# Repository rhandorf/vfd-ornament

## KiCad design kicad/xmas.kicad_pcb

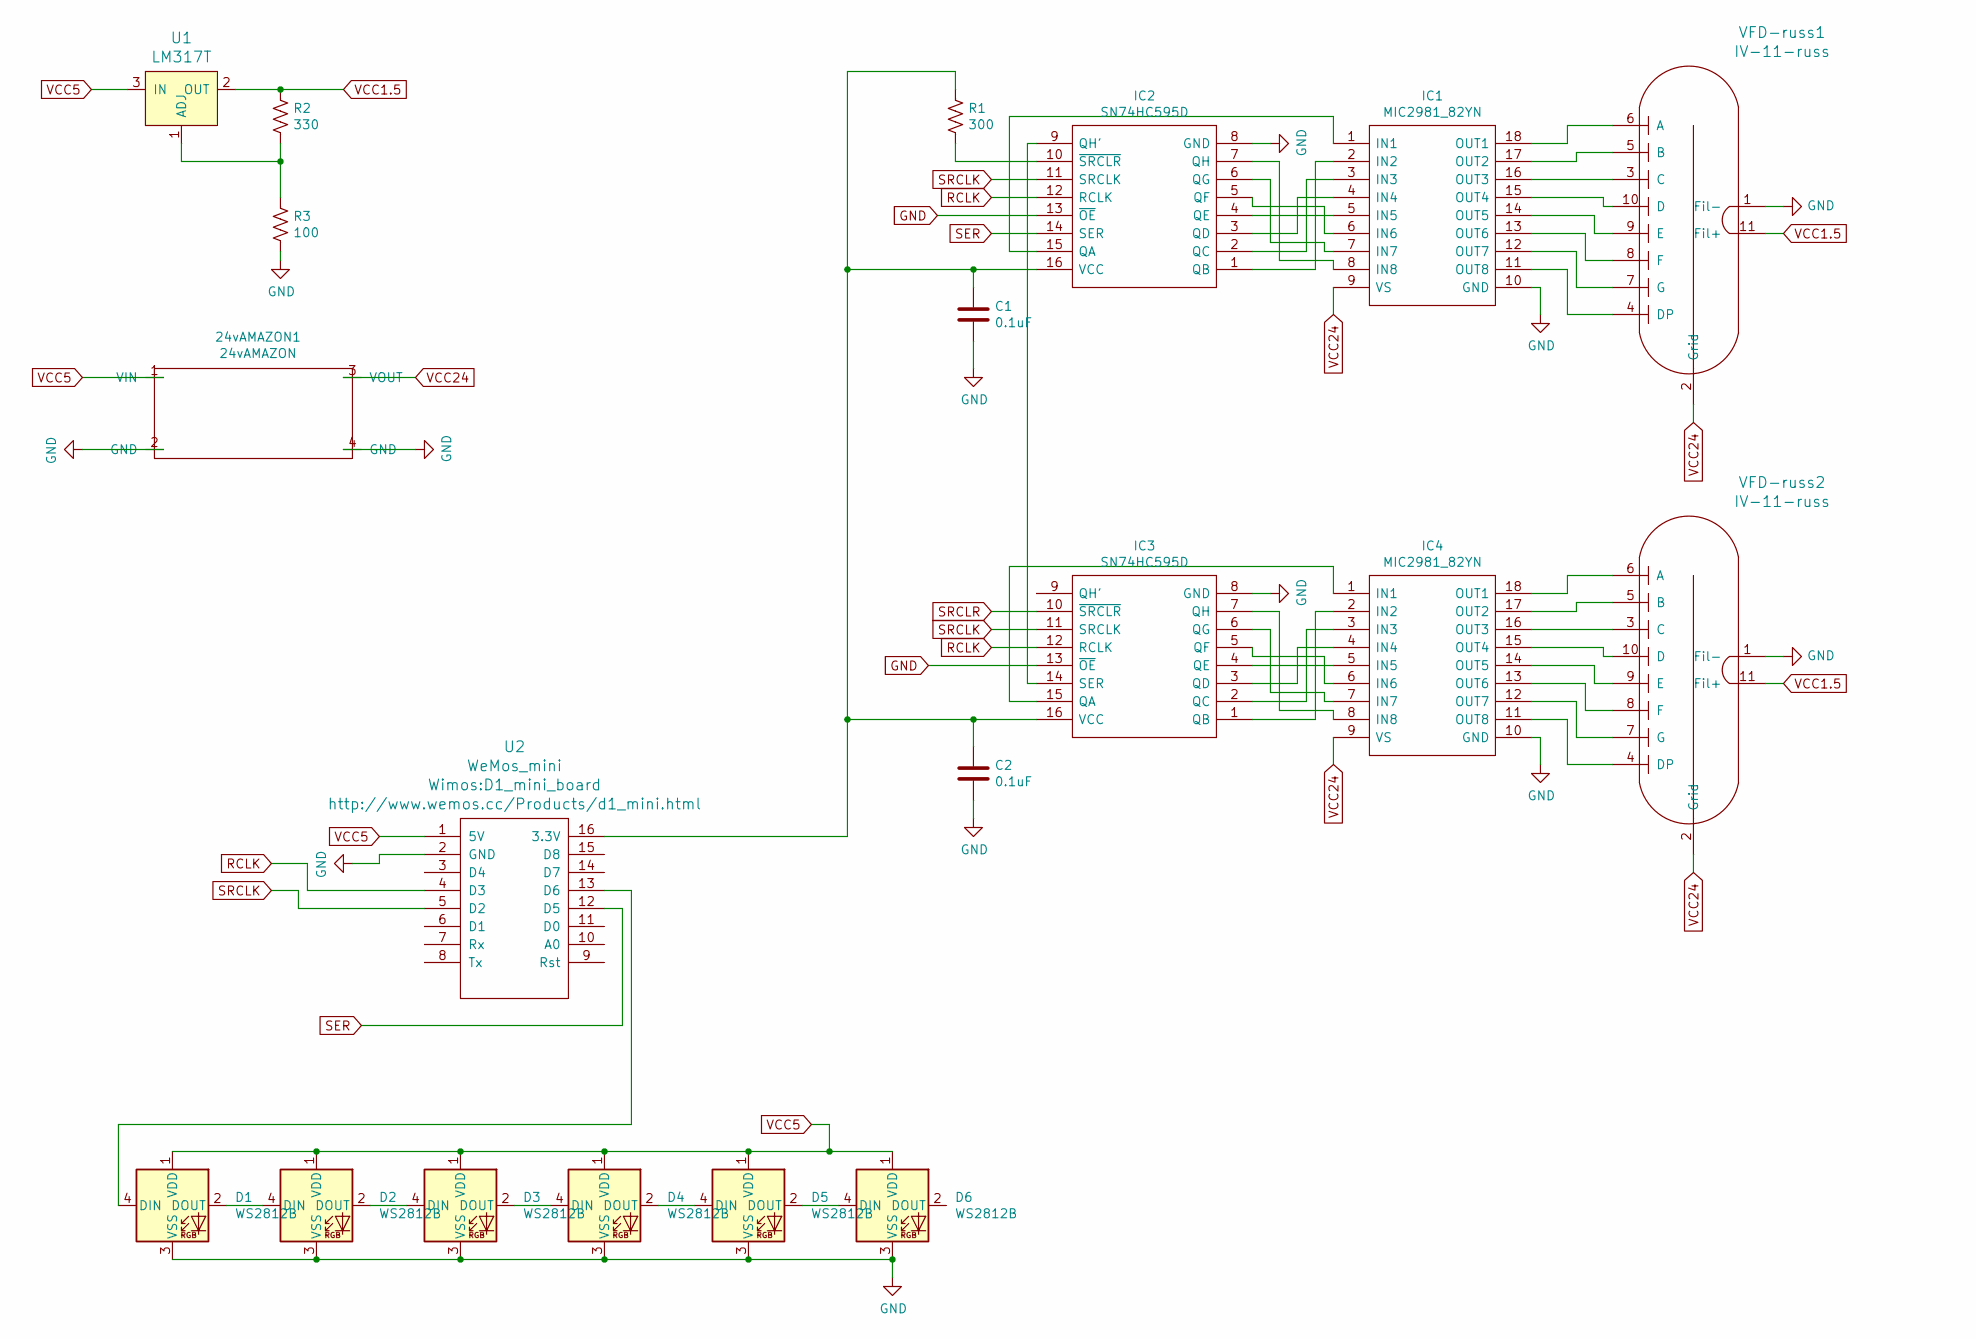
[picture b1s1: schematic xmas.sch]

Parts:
24vAMAZON1: 24vAMAZON
C1, C2: 0.1uF; C_1206_3216Metric_Pad1.42x1.75mm_HandSolder
D1, D2, D3, D4, D5, D6: WS2812B; LED_WS2812B_PLCC4_5.0x5.0mm_P3.2mm
IC1, IC4: MIC2981_82YN; DIP773W53P254L2337H394Q18N; Mouser Part Number 998-MIC2981/82YN
IC2, IC3: SN74HC595D; SOIC127P600X175-16N; Mouser Part Number 595-SN74HC595D
R1: 300; R_1206_3216Metric_Pad1.42x1.75mm_HandSolder
R2: 330; R_1206_3216Metric_Pad1.42x1.75mm_HandSolder
R3: 100; R_1206_3216Metric_Pad1.42x1.75mm_HandSolder
U1: LM317T; TO-220-3; MPN LM317T; Digi-Key_PN 497-1575-5-ND
U2: WeMos_mini; D1_mini_board
VFD-russ1, VFD-russ2: IV-11-russ

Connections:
GND: 24vAMAZON1.2 (GND), 24vAMAZON1.4 (GND), C1.2, C2.2, D1.3 (VSS), D2.3 (VSS), D3.3 (VSS), D4.3 (VSS), D5.3 (VSS), D6.3 (VSS), IC1.10 (GND), IC2.8 (GND), IC2.13 (~OE), IC3.8 (GND), IC3.13 (~OE), IC4.10 (GND), R3.2, U2.2 (GND), VFD-russ1.1 (Fil-), VFD-russ2.1 (Fil-)
unnamed: C1.1, C2.1, IC2.16 (VCC), IC3.16 (VCC), R1.1, U2.16 (3.3V)
unnamed: D1.2 (DOUT), D2.4 (DIN)
unnamed: D1.4 (DIN), U2.13 (D6)
unnamed: D2.2 (DOUT), D3.4 (DIN)
unnamed: D3.2 (DOUT), D4.4 (DIN)
unnamed: D4.2 (DOUT), D5.4 (DIN)
unnamed: D5.2 (DOUT), D6.4 (DIN)
unnamed: IC1.1 (IN1), IC2.15 (QA)
unnamed: IC1.2 (IN2), IC2.1 (QB)
unnamed: IC1.3 (IN3), IC2.2 (QC)
unnamed: IC1.4 (IN4), IC2.3 (QD)
unnamed: IC1.5 (IN5), IC2.4 (QE)
unnamed: IC1.6 (IN6), IC2.5 (QF)
unnamed: IC1.7 (IN7), IC2.6 (QG)
unnamed: IC1.8 (IN8), IC2.7 (QH)
unnamed: IC1.11 (OUT8), VFD-russ1.4 (DP)
unnamed: IC1.12 (OUT7), VFD-russ1.7 (G)
unnamed: IC1.13 (OUT6), VFD-russ1.8 (F)
unnamed: IC1.14 (OUT5), VFD-russ1.9 (E)
unnamed: IC1.15 (OUT4), VFD-russ1.10 (D)
unnamed: IC1.16 (OUT3), VFD-russ1.3 (C)
unnamed: IC1.17 (OUT2), VFD-russ1.5 (B)
unnamed: IC1.18 (OUT1), VFD-russ1.6 (A)
unnamed: IC2.9 (QH'), IC3.14 (SER)
unnamed: IC2.10 (~SRCLR), R1.2
unnamed: IC3.1 (QB), IC4.2 (IN2)
unnamed: IC3.2 (QC), IC4.3 (IN3)
unnamed: IC3.3 (QD), IC4.4 (IN4)
unnamed: IC3.4 (QE), IC4.5 (IN5)
unnamed: IC3.5 (QF), IC4.6 (IN6)
unnamed: IC3.6 (QG), IC4.7 (IN7)
unnamed: IC3.7 (QH), IC4.8 (IN8)
unnamed: IC3.15 (QA), IC4.1 (IN1)
unnamed: IC4.11 (OUT8), VFD-russ2.4 (DP)
unnamed: IC4.12 (OUT7), VFD-russ2.7 (G)
unnamed: IC4.13 (OUT6), VFD-russ2.8 (F)
unnamed: IC4.14 (OUT5), VFD-russ2.9 (E)
unnamed: IC4.15 (OUT4), VFD-russ2.10 (D)
unnamed: IC4.16 (OUT3), VFD-russ2.3 (C)
unnamed: IC4.17 (OUT2), VFD-russ2.5 (B)
unnamed: IC4.18 (OUT1), VFD-russ2.6 (A)
unnamed: R2.2, R3.1, U1.1 (ADJ)
RCLK: IC2.12 (RCLK), IC3.12 (RCLK), U2.4 (D3)
SER: IC2.14 (SER), U2.12 (D5)
SRCLK: IC2.11 (SRCLK), IC3.11 (SRCLK), U2.5 (D2)
VCC1.5: R2.1, U1.2 (OUT), VFD-russ1.11 (Fil+), VFD-russ2.11 (Fil+)
VCC5: 24vAMAZON1.1 (VIN), D1.1 (VDD), D2.1 (VDD), D3.1 (VDD), D4.1 (VDD), D5.1 (VDD), D6.1 (VDD), U1.3 (IN), U2.1 (5V)
VCC24: 24vAMAZON1.3 (VOUT), IC1.9 (VS), IC4.9 (VS), VFD-russ1.2 (Grid), VFD-russ2.2 (Grid)

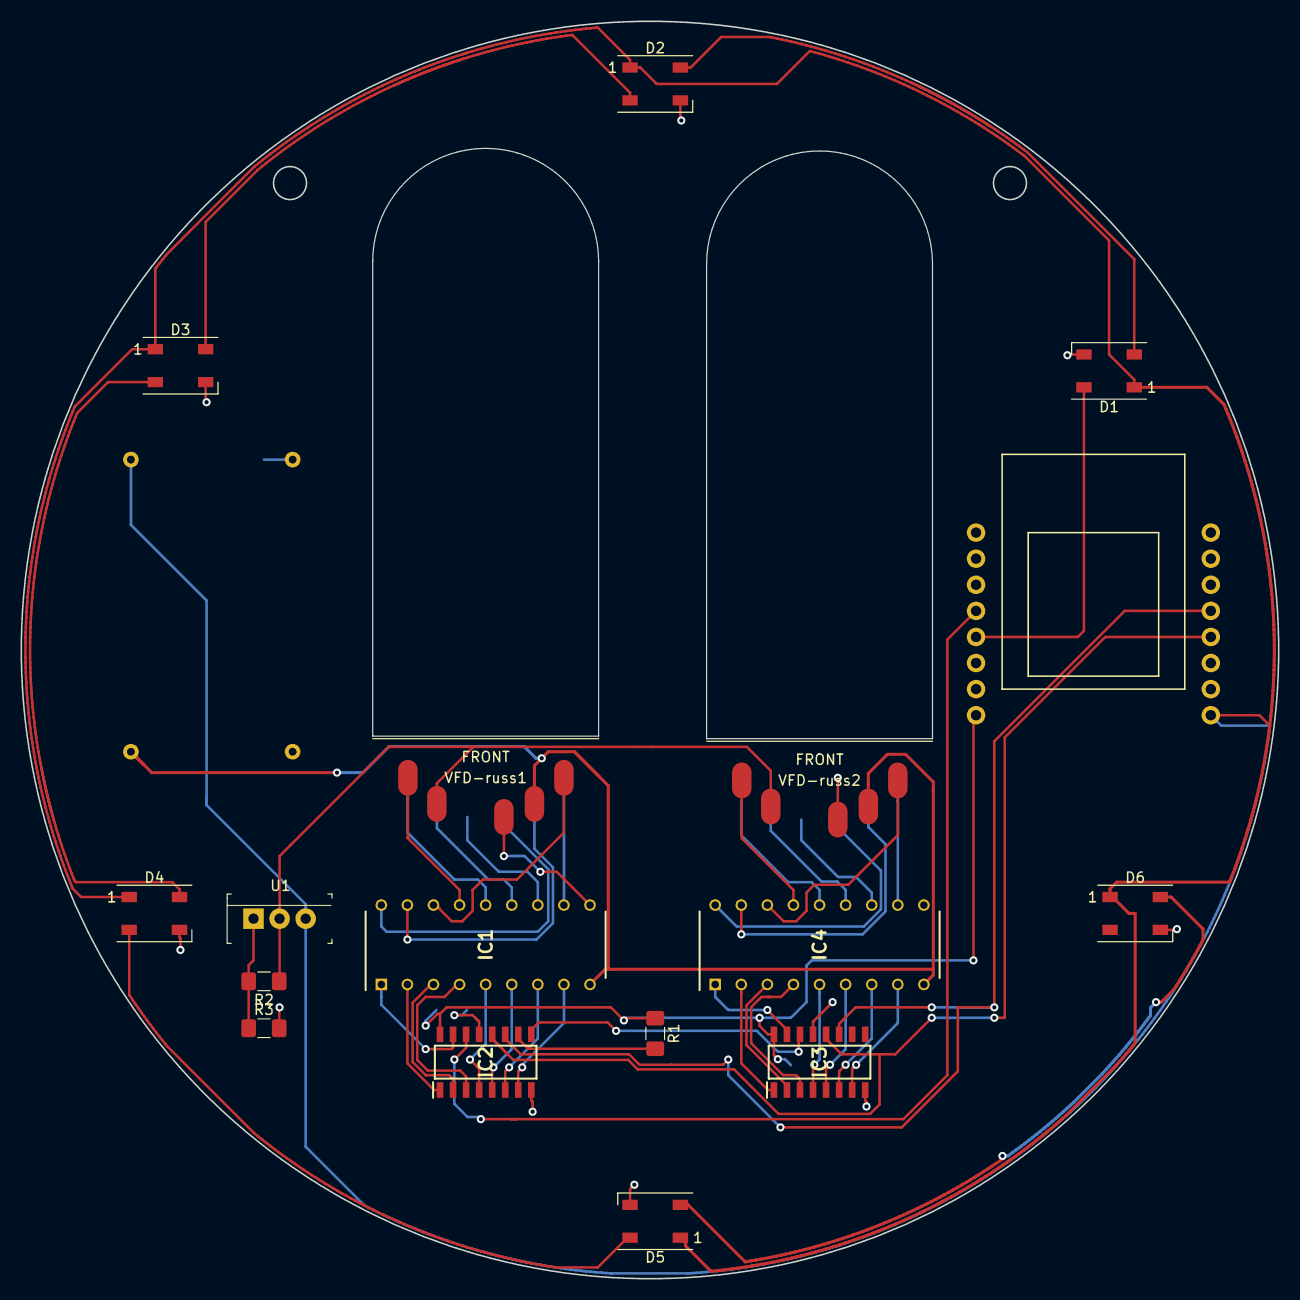
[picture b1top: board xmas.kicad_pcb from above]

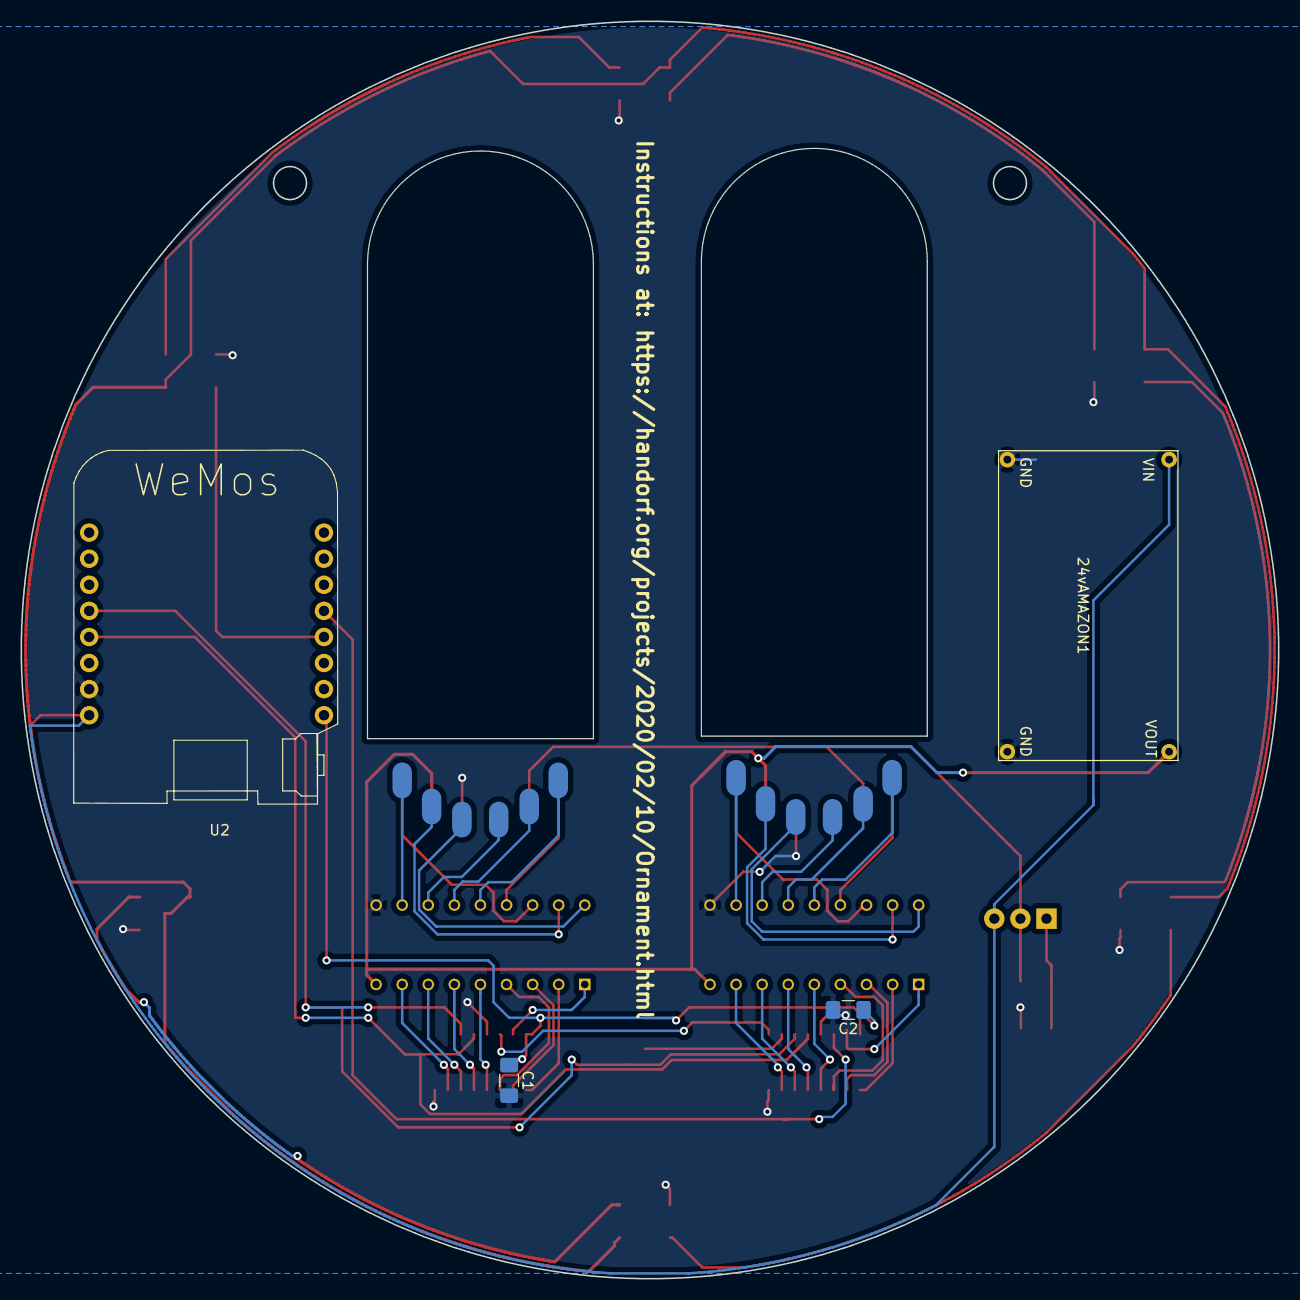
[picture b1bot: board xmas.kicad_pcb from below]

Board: 2 copper layers, 122.4 x 122.4 mm, 20 parts (4 on the bottom side), 49 nets.

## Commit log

2020-02-16 foist
2020-04-28 Updated code
2020-05-22 new wifi mgmt
2020-05-24 quick tube test
2021-02-05 new bits n fixes
